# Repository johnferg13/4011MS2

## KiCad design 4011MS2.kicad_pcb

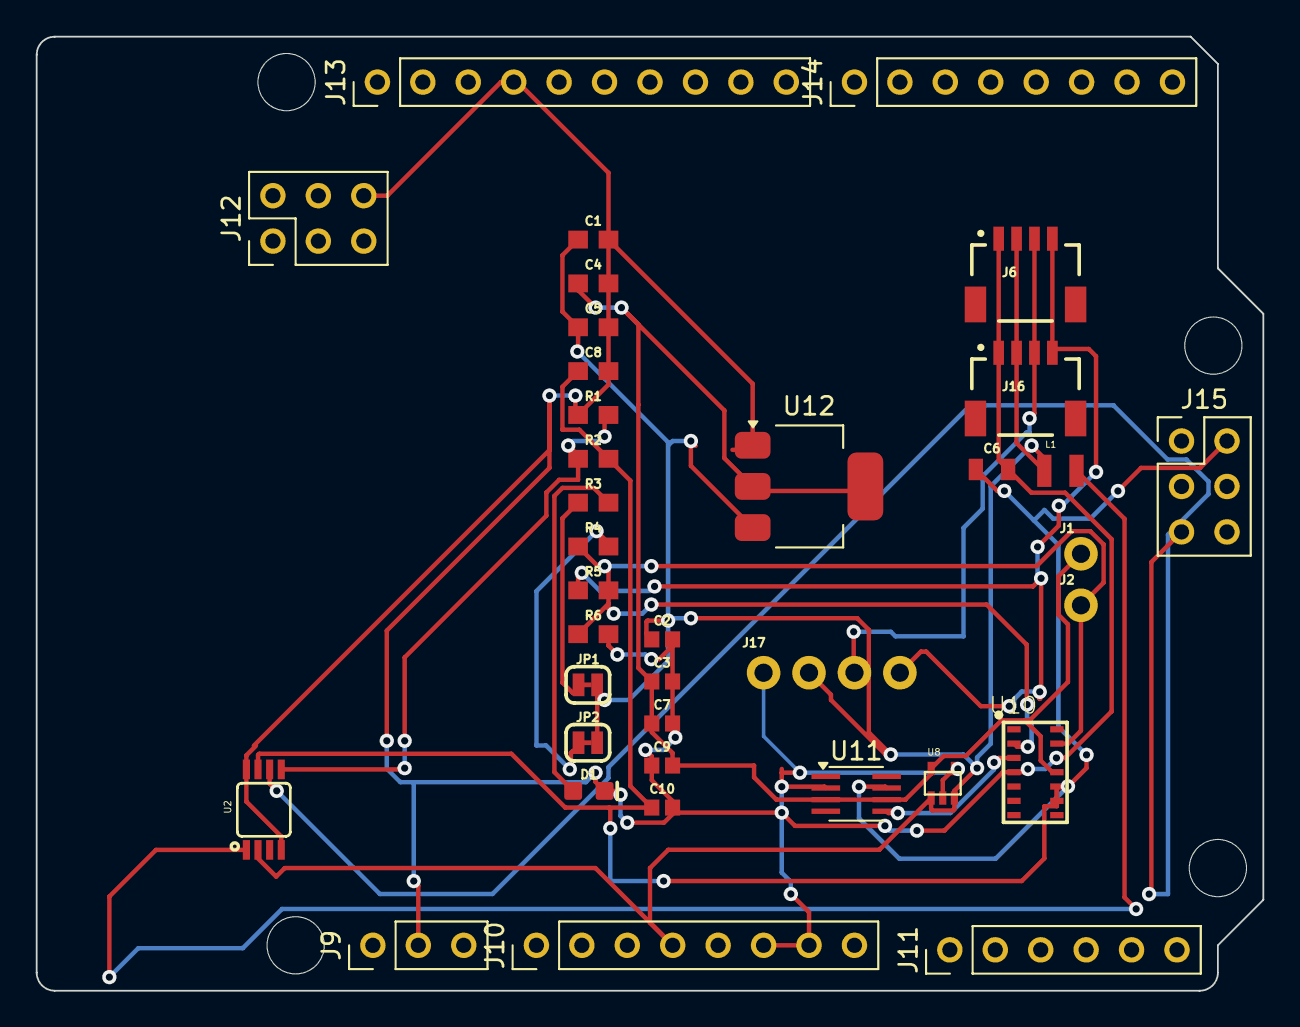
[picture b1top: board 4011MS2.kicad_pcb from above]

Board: 2 copper layers, 68.6 x 53.3 mm, 41 parts (0 on the bottom side), 13 nets.

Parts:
C1, C4, C5, C8: 10uF; 0603
C2, C3, C7, C9, C10: 0.1uF; 0402
C6: 22uF; 0805
D1: RED; LED-0603
H1, H2, H3, H4: MountingHole_Arduino; Arduino_MountingHole
J1, J2: CONN_01PTH; 1X01_NO_SILK
J6: PTH; JST04_1MM_RA
J9: OFF; Arduino_PinSocket_1x03_P2.54mm_Vertical
J10: Analog1; Arduino_PinSocket_1x08_P2.54mm_Vertical
J11: Analog2; Arduino_PinSocket_1x06_P2.54mm_Vertical
J12: ESP32; Arduino_PinSocket_2x03_P2.54mm_Vertical
J13: Digital1; Arduino_PinSocket_1x10_P2.54mm_Vertical
J14: Digital2; Arduino_PinSocket_1x08_P2.54mm_Vertical
J15: ICSP; Arduino_PinSocket_2x03_P2.54mm_Vertical
J16: QWIIC_RA; JST04_1MM_RA
J17: PTH; 1X04_NO_SILK
JP1: LED; SMT-JUMPER_2_NC_TRACE_SILK
JP2: INT; SMT-JUMPER_2_NC_TRACE_SILK
L1: 2.2μH; 0806
R1: 100k; 0603
R2: 750K; 0603
R3: 1k; 0603
R4: 4.7k; 0603
R5: 3.2k; 0603
R6: 1.8k; 0603
U2: PAM2306AYPAA; MSOP8
U8: 1.8V/100mA; SC70
U10: MAX30102; 14_PIN_OESIP
U11: TXS0102DCT; SSOP-8_2.95x2.8mm_P0.65mm
U12: LD1117S18TR_SOT223; SOT-223-3_TabPin2

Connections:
1.8V: C3.1, C4.1, C7.1, C9.2, J1.1, U8.5 (OUT), U10.P11 (VDD), U11.3 (VCCA), U11.6 (OE), U12.2 (VO)
3.3V: C1.1, C2.1, C5.1, J6.2, J10.4 (+3V3), J16.2, J17.2, JP1.2, JP2.2, L1.1, U2.2 (EN), U2.3 (VIN), U8.1 (IN), U8.3 (EN), U12.3 (VI)
5V: C6.1, C8.1, C10.1, J15.2 (+5V), R2.2, U2.7 (OUT), U10.P9 (VDD_LED), U10.P10 (VDD_LED), U11.7 (VCCB)
/SDA: J6.3, J16.3, J17.3
GND: C1.2, C2.2, C3.2, C4.2, C5.2, C6.2, C7.2, C8.2, C9.1, C10.2, D1.C, J6.1, J9.2 (GND), J10.6 (GND), J10.7 (GND), J12.6 (GND), J13.4 (GND), J16.1, J17.1, R1.1, R6.2, U2.4 (AGND), U2.8 (PGND), U8.2 (GND), U8.4 (BP), U10.P4 (GND), U10.P12 (GND), U11.2 (GND), U12.1 (GND)
LV_INT: J2.1, R4.1, R5.2, R6.1, U10.P2 (SCL), U10.P3 (SDA), U10.P13 (~INT), U11.1 (B2), U11.4 (A2), U11.5 (A1)
MC_SCL: J6.4, J16.4, J17.4, R5.1
unnamed: D1.A, R3.2
unnamed: JP1.1, R3.1
unnamed: JP2.1, R4.2
unnamed: J15.5 (RESET), U2.6 (RSET)
unnamed: R1.2, R2.1, U2.5 (FB)
unnamed: L1.2, U2.1 (LX)
